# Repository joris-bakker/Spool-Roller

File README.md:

# Spool-Roller (Made by Josua T. and Joris Bakker)

- ToDO: Nach Manual-Menu Stop, wenn man wieder zurückgeht, den Screen aktualisieren!
- Gehäuse für Platine
- 3D-Files hochladen 

All designs, CAD-Files and mechanical parts and were created by Josua T.

Software and PCB was made by Joris Bakker

# Device Function Description

The device is designed for winding various materials, such as wire, filament, or cable.  
The basic principle is based on two main components:

- **Guide Unit**: Moves smoothly back and forth to ensure the material is wound neatly and in parallel.  
- **Drive Roller**: Winds the material onto the spool.

This technology allows spools to be filled automatically and evenly.

---

## Operating Modes

### 1. Automatic Mode

The user specifies the following parameters:

- Number of windings  
- Wire diameter  
- Spool width  

The winding process is fully automated according to the set values.  
This mode is particularly suitable for manufacturing custom spools, such as induction coils.

---

### 2. Manual Mode

- No input of winding data required.  
- The winding speed is manually controlled via a rotary knob.

---

## Operating Instructions

### 1. Preparation

1. Power on the device.  
2. Select one of the two operating modes (Automatic or Manual) via the menu.  
3. If necessary, set the parameters (e.g., winding count, wire diameter, spool width).  

**Note:** During parameter entry, all motors are disabled and mechanically free to move.

---

### 2. Guide Zeroing

1. After entering the parameters, move the guide to the left edge of the guide rail.  
2. This position is set as the zero point.

---

### 3. Spool Preparation

1. Mount an empty spool on the device.  
   - The clamping mechanism works similarly to a lathe chuck.  
2. Thread the material (e.g., wire, filament, or cable) through the guide.  
3. Secure the material end firmly to the spool.  
4. Apply light tension to the material to ensure neat winding.

---

### 4. Starting the Winding Process

After zeroing, the selected operating mode starts automatically:

- **Automatic Mode:** Winding is performed according to the set parameters.  
- **Manual Mode:** Winding speed is controlled via the rotary knob.

---

## Software and Control Layout

### Control Concept

**Control Element:**  
All menu items are controlled via a rotary knob with a push function.

- **Rotate:** Navigate between menu items  
- **Push:** Select a menu item or confirm an entry  

**Display:**  
An OLED display shows all available functions, menus, and status messages of the device.

---

## Device Control

- **Main Switch:** Located on the device housing for turning the entire unit on/off.  
- **Power Supply:**  
  - Power adapter: 12 V, minimum 3 A output  
  - Power consumption: approx. 1.8 A during operation  

---

## Electronics Layout

- **Central Control Unit:**  
  - ESP32 microcontroller for motor control, display management, and user interaction  

- **Motor Drivers:**  
  - Two separate drivers for controlling the different motors  

- **Power Conversion:**  
  - DC-to-DC voltage converters for internal circuits and voltage adjustment  

---

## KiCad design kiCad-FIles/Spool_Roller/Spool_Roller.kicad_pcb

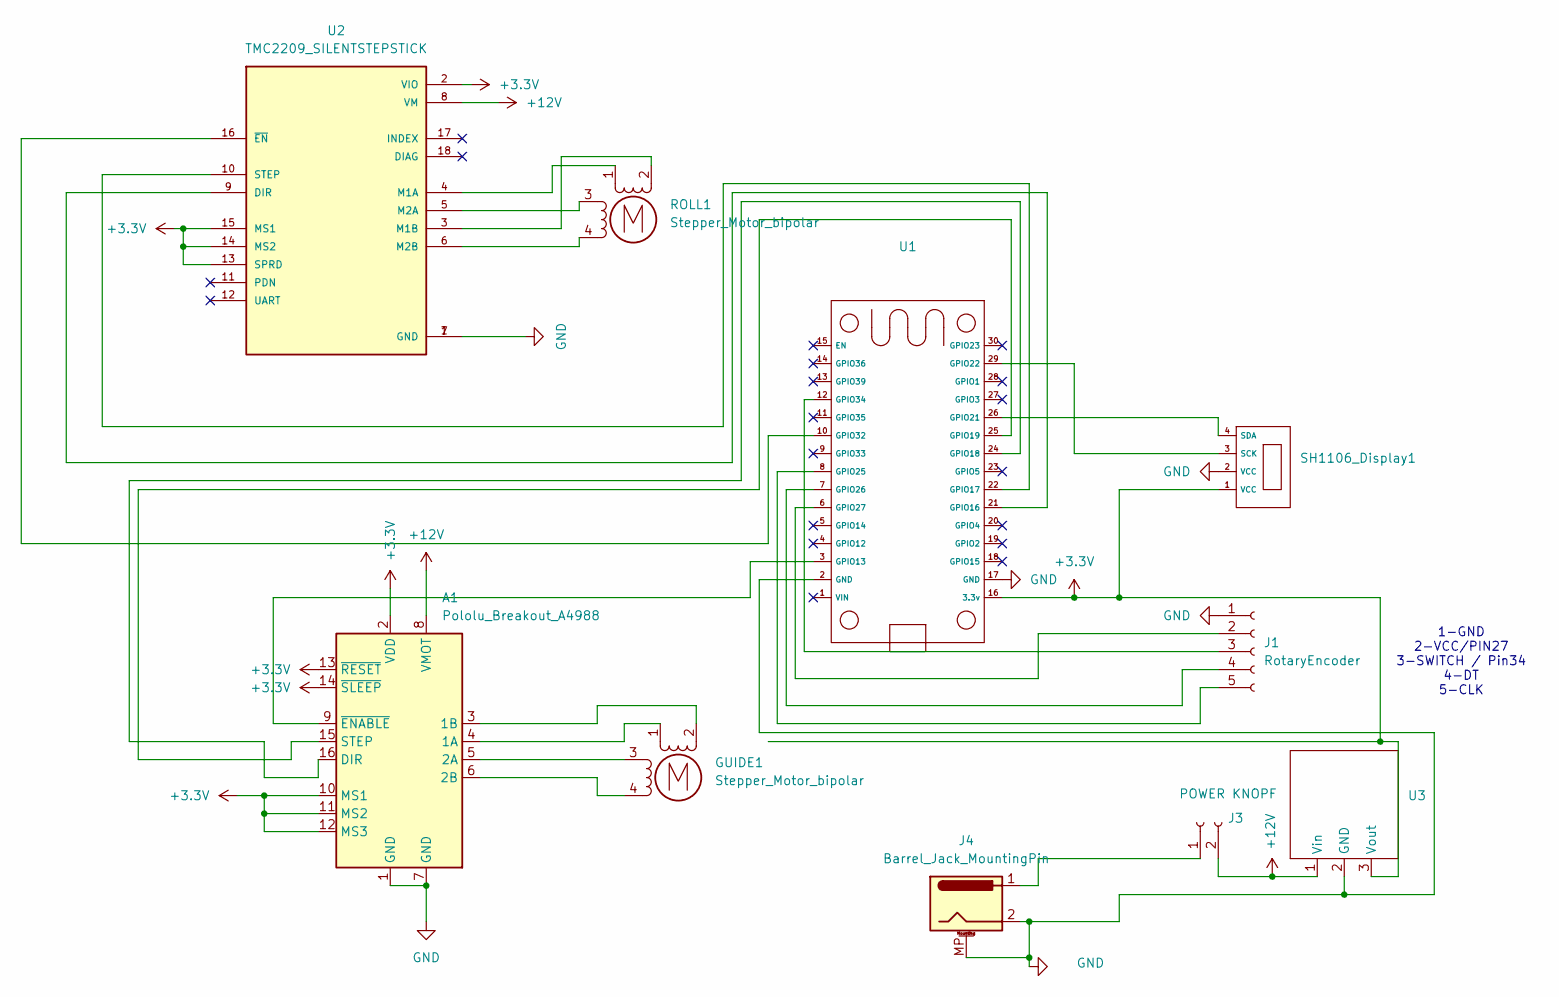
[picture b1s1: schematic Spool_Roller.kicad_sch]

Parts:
A1: Pololu_Breakout_A4988; Pololu_Breakout-16_15.2x20.3mm
GUIDE1: Stepper_Motor_bipolar; PinSocket_1x04_P2.00mm_Vertical
J1: RotaryEncoder; PinSocket_1x05_P2.54mm_Vertical
J3: POWER KNOPF; PinSocket_1x02_P2.54mm_Vertical
J4: Barrel_Jack_MountingPin; BarrelJack_Wuerth_6941xx301002
ROLL1: Stepper_Motor_bipolar; PinSocket_1x04_P2.00mm_Vertical
SH1106_Display1: PinSocket_1x04_P2.54mm_Vertical
U1: joris_esp32
U2: TMC2209_SILENTSTEPSTICK; MODULE_TMC2209_SILENTSTEPSTICK; PARTREV 1.20
U3: PinSocket_1x03_P2.54mm_Vertical

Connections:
+3.3V: A1.2 (VDD), A1.10 (MS1), A1.11 (MS2), A1.12 (MS3), A1.13 (~RESET), A1.14 (~SLEEP), SH1106_Display1.1 (VCC), U1.16 (3.3v), U2.2 (VIO), U2.13 (SPRD), U2.14 (MS2), U2.15 (MS1), U3.3 (Vout)
+12V: A1.8 (VMOT), J3.2, U2.8 (VM), U3.1 (Vin)
GND: A1.1 (GND), A1.7 (GND), J1.1, J4.2, J4.MP (MountPin), SH1106_Display1.2 (VCC), U1.2 (GND), U1.17 (GND), U2.1 (GND), U2.7 (GND), U3.2 (GND)
unnamed: A1.4 (1A), GUIDE1.1
unnamed: A1.3 (1B), GUIDE1.2 (-)
unnamed: A1.5 (2A), GUIDE1.3
unnamed: A1.6 (2B), GUIDE1.4
unnamed: A1.16 (DIR), U1.24 (GPIO18)
unnamed: A1.15 (STEP), U1.25 (GPIO19)
unnamed: A1.9 (~ENABLE), U1.3 (GPIO13)
unnamed: J1.2, U1.6 (GPIO27)
unnamed: J1.3, U1.12 (GPIO34)
unnamed: J1.4, U1.7 (GPIO26)
unnamed: J1.5, U1.8 (GPIO25)
unnamed: J3.1, J4.1
unnamed: ROLL1.2 (-), U2.3 (M1B)
unnamed: SH1106_Display1.3 (SCK), U1.29 (GPIO22)
unnamed: SH1106_Display1.4 (SDA), U1.26 (GPIO21)
unnamed: U1.21 (GPIO16), U2.9 (DIR)
unnamed: U1.22 (GPIO17), U2.10 (STEP)
unnamed: U1.10 (GPIO32), U2.16 (~EN)
unnamed: ROLL1.1, U2.4 (M1A)
unnamed: ROLL1.3, U2.5 (M2A)
unnamed: ROLL1.4, U2.6 (M2B)

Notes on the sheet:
1-GND 2-VCC/PIN27 3-SWITCH / Pin34 4-DT 5-CLK

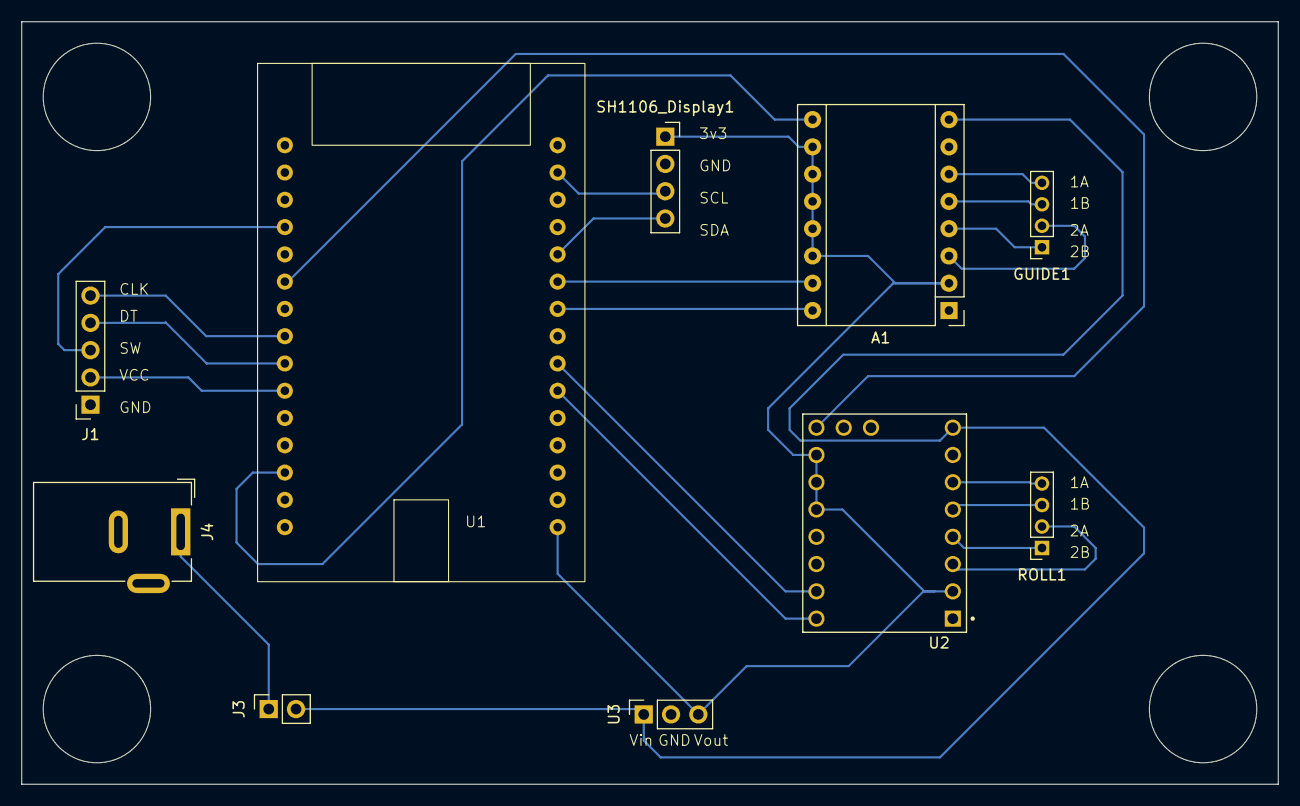
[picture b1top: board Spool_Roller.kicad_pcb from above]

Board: 2 copper layers, 117.0 x 71.0 mm, 10 parts (0 on the bottom side), 24 nets.

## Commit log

2025-08-04 Software_Cocde
    the complete software code, but not completed code
2025-08-04 kicad_files_unfinised
    its not ready yet
2025-08-14 gerberfiles, pcb, software
    those should be the final code, pcb etc.
2025-08-14 yeee
2025-09-02 Create ReadMe.md.txt
    neuer Ordner
